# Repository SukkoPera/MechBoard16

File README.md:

# MechBoard16

MechBoard16 is a mechanical keyboard for the Commodore 16.

## Summary
This project was born out of my dream of being able to build a complete Commodore 16 computer from scratch. While you can already build [the full circuit board](https://github.com/SukkoPera/LittleSixteen) from off-the-shelf-components only and put that in a case you can buy new on the market (either [Breadbin](https://www.retrofuzion.com/products/breadbin-case-set) or [C64c-style](https://icomp.de/shop-icomp/en/shop/product/c64c-case.html)), you would then have to complete that by stealing a keyboard from an original machine (and no, VIC-20/C64 keyboards won't work and there isn't much we can do in that regard, unless we patch the KERNAL and a ton of software). So I just set to rectify that.

Now, while I'm not too fussy when it comes to keyboards, give me anything that works and I'll be happy (although you probably wouldn't want to be one of the witnesses of the third time I typed *rep* on a keyboard with a misworking <kbd>G</kbd>...), making the new C16 keyboard a mechanical one looked to be the best choice for a number of reasons:
- Some good soul has already done that for the C64: he did the basic design, took all the relevant measurements, thought about all the parts needed and - best of all - he openly shared all of his notes and materials about the process. Since his original project fits the Breadbin C64 and the C16 case is basically the same, this means that, in principle, I could recycle 90% of his work and just design a new PCB featuring the C16 keyboard matrix. So all hail to MtnBuffalo and his <a href="https://www.breadbox64.com/MechBoard64-2/">MechBoard64 project</a>, this wouldn't be a reality without his job, isn't openness great?
- Well, designing a membrane keyboard would actually be harder for an amateur (all membranes are custom, how do I design and get one produced?) and lead inferior results.
- There is an incredible variety of mechanical keyswitches and keycaps around, yielding endless customization possibilities.
- I didn't know anything about mechanical keyboards, so it would just be fun to learn about them and finally own one at last.

## Assembly
The documentation from MtnBuffalo is pretty detailed, so please refer to that but first have a look at the following notes from myself.

### Circuit Board
The **circuit board** is the electrical heart of the keyboard and is the only component that needs to be different from the one used in MechBoard64 since the C16 and C64 use different keyboard matrices, despite the nearly identical key layout.

The MechBoard64 PCB was designed in a non-open format, so I redid it all in KiCad and while I was at it, I decided to add some improvements:
- I added a diode for every key. In theory, this allows for every key to be read properly, without *ghosting* issues. Still, the KERNAL applies a *blocking* algorithm so, in practice, nothing will change in this regard.
- BUT I also added a microcontroller with USB capabilities (ATmega32U4) and connected it to all the keyboard rows and columns. This mean the whole thing can be a *N-Key Rollover* USB keyboard, which will probably be useful for those people who want to use it with emulators. And keep in mind that since you have full control on the software, it can also appear as a VIC-20/C64 keyboard over USB!
- MechBoard64 has a version with LEDs, but all LEDs are driven in parallel, resulting in a huge current draw. I don't particularly care about LEDs but I decided to throw them in while I was at it, and since I would have a microcontroller onboard anyway, I decided to drive them through a MAX7219/7221 chip: this allows for individual LED control, much reduced power draw (the LEDs are multiplexed), brightness control and maximum brightness setting through a single resistor.
- I have slightly revised the Shift Lock circuit: this is necessary because latching key switches are uncommon, so one cannot be found, the behavior of the original key must be achieved through electronics. Make sure to set the JP2 and JP3 jumpers according to whether you managed to find a real latching key switch or you are using an ordinary (= momentary) one.

I realize not everyone might be interested in the above and in fact **it is all optional**! If you are not interested in USB and/or LEDs, just mount the key switches and bridge every diode (yes, this is annoying, sorry), ignoring all the extra components: basic keyboard functionality will still be there.

The PCB is what this GitHub project is all about and let me reinstate that it's only component that you need to change to make a MechBoard64 work on a C16. If you are already familiar with it, just grab the new PCB and go ahead with the build!

### Firmware
If you have installed the ATmega32U4 microcontroller, you will need to flash some firmware on it: this is available [in a separate repository](https://github.com/SukkoPera/Mechware16) and is based on the Arduino platform, so you will need the [Arduino software](https://www.arduino.cc/en/software/) to flash it. I used legacy version 1.8.19 so I can only guarantee that that one works, if you use a newer one or the web-based IDE you are on your own.

You will need to install the bootloader first. For this you will need an ICSP programmer, which you can buy cheaply on AliExpress or similar sites. The ICSP connector is marked as J202 on the board. Select the _Arduino Micro_ board in the IDE and proceed as normal. Once that is done, the firmware can be flashed through USB connector J201 as if the whole thing were a normal Arduino Micro board. Make sure to install the dependencies first.

### Metal Bracket
The board will need to be fastened to the top part of the case somehow, and this is done through a **metal bracket** which doubles as a keyboard plate.

I have designed [my own bracket](https://github.com/SukkoPera/MechPlate16) based on MtnBuffalo's instructions, but since I strived to maintain the same position for all of the key and screw holes, you should be able to use this board with the plate that was designed for the MechBoard64: you can get it through a Chinese company as MtnBuffalo recommends or ask other manufacturers.

### Screws
To fasten the two things together, you will need **screws**: MtnBuffalo recommends *six plastic M3 x 10 mm screws, six plastic M3 bolts and six plastic M3 x 3mm spacers (ø=6 mm)*. I used *metal* screws of the same dimensions and plastic spacers with an outside diameter of 5 mm, putting some insulation tape on the washers in order to avoid them shorting tracks on the PCB.

### Key Switches
At this point you will have a nice keyboard prototype without keys, so you will need to solder exactly 66 **key switches** into it. This is the point where your customization options start: MtnBuffalo used *Gateron Yellow* switches as he thought they yield a very similar experience to the original keys. Personally, I don't think we should necessarily aim at replicating the original experience, so I'd recommend feeling free to use different switches.

While the keyboard was designed for Cherry MX keyswitches, these days maaaany manufacturers make compatible ones: I think the most respected alternative manufacturers are <a href="https://www.gateron.com">Gateron</a> and <a href="https://www.kailh.net">Kailh</a>. *Durock* is another well-known brand and, even though I don't think it's a particularly smart idea to save 10€ on a project that will cost you around 100€ anyway, there are also cheaper options: *Outemu* is a Chinese brand that seems to have its fans, while *Redragon* is the cheapest I could find (less than 10€ for 150 keyswitches - more than enough for 2 keyboard - shipped to Europe!) and their Red switches look definitely better to me, than what the price would suggest.

Here are a few links to online shops where you can find an ample offering of key switches:
- [Keychron](https://www.keychron.com)
- [CannonKeys](https://cannonkeys.com/collections/switches)

Even by just skimming through these shops, it is easy to get lost for those like me who might not be too much into keyboards, so here's some help: first of all, you need *standard/normal profile* switches, don't get *low profile* ones.

Second: there are 3 main types of switches, giving different "press feelings": the most common type is *linear* and the original keys are of this type (get this if you are undecided). It means that the key can be pressed with a constant pressure until it comes to a halt. Some people prefer to feel a "bump" when the key triggers, so they'd better look for switches of the *tactile* type (personally, I find this to be really annoying unless you are used to it). Finally, I have a thing for *clicky* switches, which make a rather loud click when they trigger (this is what most people find annoying, but when your ordinary keyboard is a 122-key "battlecruiser" Model M...).

Then it basically gets down to how hard you want to push your keys, which is measured in grams: generally 35g is the softest option, while 80g is the stiffest you can get.

These two parameters we just mentioned are usually reflected in the color of the switch *stem*. There is some informal standard across manufacturers for this (derived from the original Cherry MX catalogue, I think), but always double check: blue is for clicky switches, red is for soft linears, black is for stiff linears, etc.

Speaking of the stem, you'll notice that the MX stem is a simple cross. Sometimes the cross might include walls on its sides or all around: these are just for dust protection, which seems totally redundant to me but there you go. Just make sure it's still MX-compatible.

MX-compatible key switches can have two different mounting styles, *PCB* or *plate*: the former are for keyboards that do not use a plate and come with two extra side prongs that help positioning the key switch correctly and securing it in place. Plate-mount switches lack these prongs, since their job will be done by the hole in the plate. MechBoard64 requires plate-mount switches or that you cut the extra prongs (it's just plastic), while **MechBoard16 has extra holes** and will thus accept both types.

One final tip is that there is a tendency to use stiffer switches for the spacebar, since it is generally pressed with more force. So if you choose *Red* switches, you might want to use a *Black* one for the spacebar. Due to my clicky thing, I used *Gateron Blue*'s but I went with a *Green* for my spacebar.

### Keycaps
The key switches look all boringly the same, so you'll probably want to stick some **keycaps** on their stem*. I was quite surprised when I found out that almost all keycaps ever made are the same size, so **in principle** you could use any keycaps having MX connection style. In reality, you are bound to the original Commodore keycaps: this is because most of the wider keycaps (<kbd>CTRL</kbd>, <kbd>CLEAR/HOME</kbd>, <kbd>SHIFT</kbd> and the Function keys) on the original keyboard have their stem receptacles off-center while contemporary keycaps, on the contrary, have the receptacles centered.

There are more problems in using modern keycaps by the way: for instance, the original Commodore spacebar is 9U, while contemporary spacebars are shorter (I think they don't go over 7U). Most modern keycaps also have different profiles for different rows (the originals are all the same) and not all sizes are available for all rows: as an example, for the Function keys you'll need 1.5U keycaps, one per row, but modern keycaps only come in 1.5U for rows 1 and 3.

Since working around all these issues requires more thought and since the MechBoard64 simply used the original Commodore placement, for the first MechBoard16 release I decided to follow suit but things might change in the future, once I'm sure all the rest is correct.

The bottom line is that **at the moment you still need to recover the keys from an original C16 keyboard**. Keys from a VIC-20 or C64 keyboard should work just as well, despite having some labeling differences (<kbd>RESTORE</kbd> is <kbd>CLEAR/HOME</kbd>, the arrow keys are missing, etc.). Some people have actually produced new C64 keys but they didn't plan alternative labeling for us C16 users and apparently those keys were even only sold through Kickstarter-style initiatives and are not on regular sale (yet?).

### Keycap Adapters
It looked easy after all, didn't it? Unfortunately, the original Commodore keycaps do not have MX-style stems, so you'll need some **adapters**. These must be 3D-printed, use the STL file provided by MechBoard64.

### Stabilizers
The wider keys (<kbd>RETURN</kbd> and <kbd>SPACE</kbd>) are too large for a single keyswitch and would *bind* (get stuck) unless hit close to the center. In order to avoid that, thin metal bars are used to attach them to the keyboard plate for the whole length. These are called **stabilizers** and again, come in different styles. MechBoard64 went for the so-called *Costar stabilizers* and we did the same: these can be bought on the market and come as a kit of plastic clips that must be inserted in the slots available on the plate, a set of key inserts and some bent metal wire that goes inbetween.

Unfortunately, the original Commodore spacebar is too wide for the stabilizer kits that are currently available commercially so, while you can use the clips and inserts, you will need to bend some metal wire with the correct proportions. MtnBuffalo used 1 mm steel wire bent with a tool named EZ Bender and I was able to buy both things at a model shop (I was told they are commonly used by model airplane enthusiasts, if that helps). The EZ Bender was about 30€ and the wire is inexpensive (buy it straight, not in a spool!).

### Cables
This is the easy part: just get a bunch of those *Dupont wires* people use for Arduino projects: you'll need 20 female-to-female, they're cheap and you can find them everywhere. You'll probably find them with individual connectors only but oh well... As for the length, 20 cm should be fine.

The above assumes that a 90-degree male pin header is soldered at CN1, but you can also solder a female header and use male-to-female wires if so you prefer.

Oh, and while we're at it, CN2 on the board allows for connection of the keyboard to a Plus/4 computer: while this makes little sense, as the Plus/4 has a totally different form factor in which the keyboard cannot fit, it could still be useful for temporary use or whatever. Maybe someone will re-layout the board in the proper format? ;)

### LEDs
If you want LEDs, you can solder one per each key. The required diameter is 3 mm. I'd recommend using high-brightness ones.

Remember to tune R207 according to the LEDs you choose and brightness you like.

To tune the brightness to your liking, you first need to change R207 according to table 11 of the [MAX7219/7221 datasheet](https://www.analog.com/media/en/technical-documentation/data-sheets/max7219-max7221.pdf). This will set the maximum brightness of the LEDs of all keys except <kbd>SHIFT</kbd>, <kbd>SHIFT LOCK</kbd> and <kbd>SPACE</kbd>. The actual brightness can be fine-tuned through some hotkeys (see below).

Due to its length, the spacebar has 3 LEDs which are linked together: they are all either ON or OFF at any given moment. The same goes for the LEDs for the two <kbd>SHIFT</kbd> keys. The brightness for these is controlled by resistors R208, 209, 210, 211 and 212. These can all be set to the same value, which you should calculate depending on the Vf of the LEDs you are using and the current you set with R207, so that these LEDs have the same brightness as the other ones.

The LED for the <kbd>SHIFT LOCK</kbd> key only lights up when the lock is enabled. Its brightness is controlled by R3, set it to same value as R208/etc., unless you are using a different led for this key.

Since I was tired of having to disconnect both the keyboard and the case LED every time I had to open the machine, I added a connector so that the case LED can be connected to the keyboard board, namely R204, black wire goes to GND. You can even replace the built-in LED with an RGB one and set it to your favourite color by picking appropriate values for R204/205/206 (for R/G/B respectively). This LED can also be controlled by the software running on the microcontroller, so maybe it could be used for signalling some events. Note that the R204 will not do anything if the ATmega32U4 microcontroller is not mounted.

### HotKeys
The firmware supports some hotkeys, all triggered by pressing <kbd>CTRL</kbd> + <kbd>C=</kbd> + a third key, as follows:
- <kbd>F1</kbd>: Turn all LEDs permanently OFF.
- <kbd>F2</kbd>: Turn all LEDs permanently ON.
- <kbd>F3</kbd>: Turn all LEDS OFF, but turn ON those corresponding to the keys that are being pressed.
- <kbd>F4</kbd>: Turn all LEDS ON, but turn OFF those corresponding to the keys that are being pressed.
- <kbd>1</kbd>: Set startup animation to *Chasing*.
- <kbd>2</kbd>: Set startup animation to *Scrolling Column*.
- <kbd>+</kbd>: Increase LED brightness.
- <kbd>-</kbd>: Decrease LED brightness.

## Mainboard Modification
Unfortunately a stock C16 does not feature any power pins on the keyboard connector, therefore a small modification must be made on the mainboard: just solder a wire on the back of the board as in [this picture](img/mech_power_photo.jpg). Make sure it doesn't touch the nearby pins.

Note that this could be made even easier as the large track below the keyboard connector on the board is +5V, but you would need to scrape away some insulation and I like fully reversible mods anyway.

If you are using a LittleSixteen board, this modification is not necessary since V4, just short the JP1 solder jumper.

## Disclaimer
**NOTE: I am in no way affiliated with or endorsed by any of the above-mentioned companies, shops or websites. I am only suggesting them for practical needs and to save you time.**

## Releases
If you want to get this board produced, you are recommended to get [the latest release](https://github.com/SukkoPera/MechBoard16/releases) rather than the current git version, as the latter might be under development and is not guaranteed to be working.

Every release is accompanied by its Bill Of Materials (BOM) file and any relevant notes about it, which you are recommended to read carefully.

## License
The MechBoard16 documentation, including the design itself, is copyright &copy; SukkoPera 2023-2025 and is licensed under the [Creative Commons Attribution-NonCommercial-ShareAlike 4.0 International License](https://creativecommons.org/licenses/by-nc-sa/4.0/).

This documentation is distributed *as is* and WITHOUT ANY EXPRESS OR IMPLIED WARRANTIES whatsoever with respect to its functionality, operability or use, including, without limitation, any implied warranties OF MERCHANTABILITY, SATISFACTORY QUALITY, FITNESS FOR A PARTICULAR PURPOSE or infringement. We expressly disclaim any liability whatsoever for any direct, indirect, consequential, incidental or special damages, including, without limitation, lost revenues, lost profits, losses resulting from business interruption or loss of data, regardless of the form of action or legal theory under which the liability may be asserted, even if advised of the possibility or likelihood of such damages.

## Support the Project
If you want to get some boards manufactured, you can get them from PCBWay through this link:

You get my gratitude and cheap, professionally-made and good quality PCBs, I get some credit that will help with this and [other projects](https://www.pcbway.com/project/member/shareproject/?bmbid=41100). You won't even have to worry about the various PCB options, it's all pre-configured for you!

Also, if you still have to register, [you can use this link](https://www.pcbway.com/setinvite.aspx?inviteid=41100) to get some bonus initial credit (and yield me some more).

You can also buy me a coffee if you want:

## Thanks
- MtnBuffalo for designing the original MechBoard64, making it open and being always happy to help.

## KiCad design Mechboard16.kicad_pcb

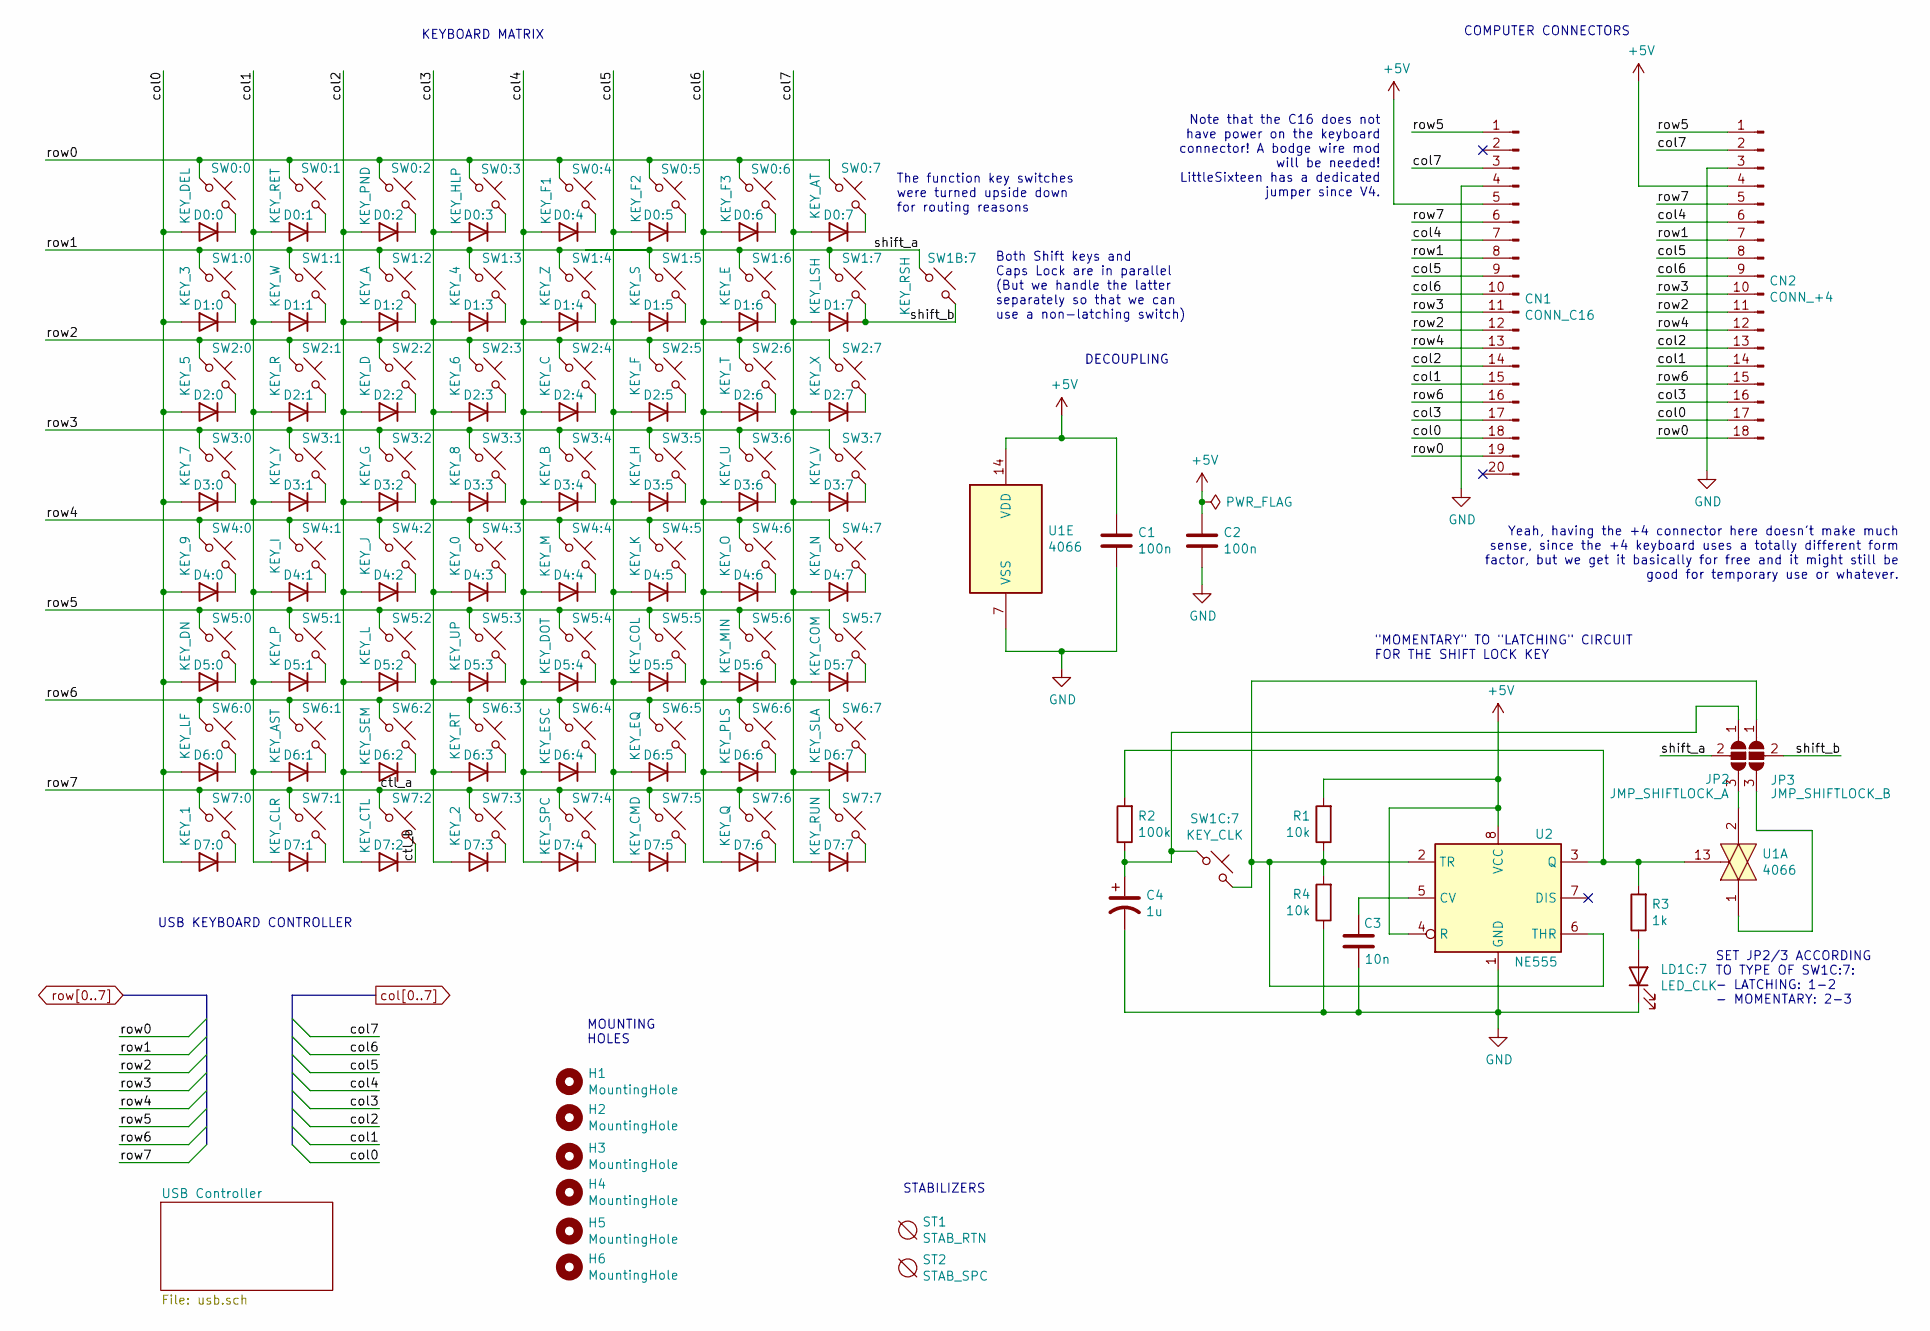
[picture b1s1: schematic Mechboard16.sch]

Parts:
C1, C2: 100n; C_0805_2012Metric_Pad1.18x1.45mm_HandSolder; LCSC C49678
C3: 10n; C_0805_2012Metric_Pad1.18x1.45mm_HandSolder; LCSC C1710
C4: 1u; C_1206_3216Metric_Pad1.33x1.80mm_HandSolder; LCSC C1848
CN1: CONN_C16; PinHeader_1x20_P2.54mm_Vertical
CN2: CONN_+4; PinHeader_1x18_P2.54mm_Vertical
D0:0, D0:1, D0:2, D0:3, D0:4, D0:5, D0:6, D0:7, D1:0, D1:1, D1:2, D1:3, D1:4, D1:5, D1:6, D1:7, D2:0, D2:1, D2:2, D2:3, D2:4, D2:5, D2:6, D2:7, D3:0, D3:1, D3:2, D3:3, D3:4, D3:5, D3:6, D3:7, D4:0, D4:1, D4:2, D4:3, D4:4, D4:5, D4:6, D4:7, D5:0, D5:1, D5:2, D5:3, D5:4, D5:5, D5:6, D5:7, D6:0, D6:1, D6:2, D6:3, D6:4, D6:5, D6:6, D6:7, D7:0, D7:1, D7:2, D7:3, D7:4, D7:5, D7:6, D7:7: 1n4148; D_SOD-323_HandSoldering; LCSC C2128
H1, H2, H3, H4, H5, H6: MountingHole; MountingHole_3.5mm
JP2: JMP_SHIFTLOCK_A; SolderJumper-3_P1.3mm_Open_RoundedPad1.0x1.5mm
JP3: JMP_SHIFTLOCK_B; SolderJumper-3_P1.3mm_Open_RoundedPad1.0x1.5mm
LD1C:7: LED_CLK; LED_MX_6028R; LCSC C3646964
R1, R4: 10k; R_0805_2012Metric_Pad1.20x1.40mm_HandSolder; LCSC C17414
R2: 100k; R_0805_2012Metric_Pad1.20x1.40mm_HandSolder; LCSC C149504
R3: 1k; R_0805_2012Metric_Pad1.20x1.40mm_HandSolder; LCSC C17513
ST1: STAB_RTN; Stabilizer_Costar_2.00u
ST2: STAB_SPC; Stabilizer_Costar_9.00u_Commodore
SW0:0: KEY_DEL; SW_Hotswap_Kailh_MX_1.00u; LCSC C41430893
SW0:1: KEY_RET; SW_Hotswap_Kailh_MX_2.00u; LCSC C41430893
SW0:2: KEY_PND; SW_Hotswap_Kailh_MX_1.00u; LCSC C41430893
SW0:3: KEY_HLP; SW_Hotswap_Kailh_MX_1.50u_OffsetL; LCSC C41430893
SW0:4: KEY_F1; SW_Hotswap_Kailh_MX_1.50u_OffsetL; LCSC C41430893
SW0:5: KEY_F2; SW_Hotswap_Kailh_MX_1.50u_OffsetL; LCSC C41430893
SW0:6: KEY_F3; SW_Hotswap_Kailh_MX_1.50u_OffsetL; LCSC C41430893
SW0:7: KEY_AT; SW_Hotswap_Kailh_MX_1.00u; LCSC C41430893
SW1:0: KEY_3; SW_Hotswap_Kailh_MX_1.00u; LCSC C41430893
SW1:1: KEY_W; SW_Hotswap_Kailh_MX_1.00u; LCSC C41430893
SW1:2: KEY_A; SW_Hotswap_Kailh_MX_1.00u; LCSC C41430893
SW1:3: KEY_4; SW_Hotswap_Kailh_MX_1.00u; LCSC C41430893
SW1:4: KEY_Z; SW_Hotswap_Kailh_MX_1.00u; LCSC C41430893
SW1:5: KEY_S; SW_Hotswap_Kailh_MX_1.00u; LCSC C41430893
SW1:6: KEY_E; SW_Hotswap_Kailh_MX_1.00u; LCSC C41430893
SW1:7: KEY_LSH; SW_Hotswap_Kailh_MX_1.50u_OffsetL; LCSC C41430893
SW1B:7: KEY_RSH; SW_Hotswap_Kailh_MX_1.50u_OffsetL; LCSC C41430893
SW1C:7: KEY_CLK; SW_Hotswap_Kailh_MX_1.00u; LCSC C41430893
SW2:0: KEY_5; SW_Hotswap_Kailh_MX_1.00u; LCSC C41430893
SW2:1: KEY_R; SW_Hotswap_Kailh_MX_1.00u; LCSC C41430893
SW2:2: KEY_D; SW_Hotswap_Kailh_MX_1.00u; LCSC C41430893
SW2:3: KEY_6; SW_Hotswap_Kailh_MX_1.00u; LCSC C41430893
SW2:4: KEY_C; SW_Hotswap_Kailh_MX_1.00u; LCSC C41430893
SW2:5: KEY_F; SW_Hotswap_Kailh_MX_1.00u; LCSC C41430893
SW2:6: KEY_T; SW_Hotswap_Kailh_MX_1.00u; LCSC C41430893
SW2:7: KEY_X; SW_Hotswap_Kailh_MX_1.00u; LCSC C41430893
SW3:0: KEY_7; SW_Hotswap_Kailh_MX_1.00u; LCSC C41430893
SW3:1: KEY_Y; SW_Hotswap_Kailh_MX_1.00u; LCSC C41430893
SW3:2: KEY_G; SW_Hotswap_Kailh_MX_1.00u; LCSC C41430893
SW3:3: KEY_8; SW_Hotswap_Kailh_MX_1.00u; LCSC C41430893
SW3:4: KEY_B; SW_Hotswap_Kailh_MX_1.00u; LCSC C41430893
SW3:5: KEY_H; SW_Hotswap_Kailh_MX_1.00u; LCSC C41430893
SW3:6: KEY_U; SW_Hotswap_Kailh_MX_1.00u; LCSC C41430893
SW3:7: KEY_V; SW_Hotswap_Kailh_MX_1.00u; LCSC C41430893
SW4:0: KEY_9; SW_Hotswap_Kailh_MX_1.00u; LCSC C41430893
SW4:1: KEY_I; SW_Hotswap_Kailh_MX_1.00u; LCSC C41430893
SW4:2: KEY_J; SW_Hotswap_Kailh_MX_1.00u; LCSC C41430893
SW4:3: KEY_0; SW_Hotswap_Kailh_MX_1.00u; LCSC C41430893
SW4:4: KEY_M; SW_Hotswap_Kailh_MX_1.00u; LCSC C41430893
SW4:5: KEY_K; SW_Hotswap_Kailh_MX_1.00u; LCSC C41430893
SW4:6: KEY_O; SW_Hotswap_Kailh_MX_1.00u; LCSC C41430893
SW4:7: KEY_N; SW_Hotswap_Kailh_MX_1.00u; LCSC C41430893
SW5:0: KEY_DN; SW_Hotswap_Kailh_MX_1.00u; LCSC C41430893
SW5:1: KEY_P; SW_Hotswap_Kailh_MX_1.00u; LCSC C41430893
SW5:2: KEY_L; SW_Hotswap_Kailh_MX_1.00u; LCSC C41430893
SW5:3: KEY_UP; SW_Hotswap_Kailh_MX_1.00u; LCSC C41430893
SW5:4: KEY_DOT; SW_Hotswap_Kailh_MX_1.00u; LCSC C41430893
SW5:5: KEY_COL; SW_Hotswap_Kailh_MX_1.00u; LCSC C41430893
SW5:6: KEY_MIN; SW_Hotswap_Kailh_MX_1.00u; LCSC C41430893
SW5:7: KEY_COM; SW_Hotswap_Kailh_MX_1.00u; LCSC C41430893
SW6:0: KEY_LF; SW_Hotswap_Kailh_MX_1.00u; LCSC C41430893
SW6:1: KEY_AST; SW_Hotswap_Kailh_MX_1.00u; LCSC C41430893
SW6:2: KEY_SEM; SW_Hotswap_Kailh_MX_1.00u; LCSC C41430893
SW6:3: KEY_RT; SW_Hotswap_Kailh_MX_1.00u; LCSC C41430893
SW6:4: KEY_ESC; SW_Hotswap_Kailh_MX_1.00u; LCSC C41430893
SW6:5: KEY_EQ; SW_Hotswap_Kailh_MX_1.00u; LCSC C41430893
SW6:6: KEY_PLS; SW_Hotswap_Kailh_MX_1.00u; LCSC C41430893
SW6:7: KEY_SLA; SW_Hotswap_Kailh_MX_1.00u; LCSC C41430893
SW7:0: KEY_1; SW_Hotswap_Kailh_MX_1.00u; LCSC C41430893
SW7:1: KEY_CLR; SW_Hotswap_Kailh_MX_1.50u_OffsetR; LCSC C41430893
SW7:2: KEY_CTL; SW_Hotswap_Kailh_MX_1.50u_OffsetL; LCSC C41430893
SW7:3: KEY_2; SW_Hotswap_Kailh_MX_1.00u; LCSC C41430893
SW7:4: KEY_SPC; SW_Hotswap_Kailh_MX_9.00u; LCSC C41430893
SW7:5: KEY_CMD; SW_Hotswap_Kailh_MX_1.00u; LCSC C41430893
SW7:6: KEY_Q; SW_Hotswap_Kailh_MX_1.00u; LCSC C41430893
SW7:7: KEY_RUN; SW_Hotswap_Kailh_MX_1.00u; LCSC C41430893
U1: 4066; SOIC-14_3.9x8.7mm_P1.27mm; LCSC C233577
U2: NE555; SOIC-8_3.9x4.9mm_P1.27mm; LCSC C5125085

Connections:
+5V: C1.1, C2.1, CN1.5, CN2.4, R1.2, U1.14 (VDD), U2.4 (R), U2.8 (VCC); also elsewhere on the board
/ctl_b: D7:2.1 (K), SW7:2.2
/shift_b: D1:7.1 (K), JP2.2 (C), SW1:7.2, SW1B:7.2
GND: C1.2, C2.2, C3.2, C4.2, CN1.4, CN2.3, LD1C:7.1 (K), R4.1, U1.7 (VSS), U2.1 (GND); also elsewhere on the board
unnamed: C3.1, U2.5 (CV)
unnamed: C4.1, JP3.1 (A), R2.1, SW1C:7.1
unnamed: D0:0.1 (K), SW0:0.2
unnamed: D0:1.1 (K), SW0:1.2
unnamed: D0:2.1 (K), SW0:2.2
unnamed: D0:3.1 (K), SW0:3.2
unnamed: D0:4.1 (K), SW0:4.2
unnamed: D0:5.1 (K), SW0:5.2
unnamed: D0:6.1 (K), SW0:6.2
unnamed: D0:7.1 (K), SW0:7.2
unnamed: D1:0.1 (K), SW1:0.2
unnamed: D1:1.1 (K), SW1:1.2
unnamed: D1:2.1 (K), SW1:2.2
unnamed: D1:3.1 (K), SW1:3.2
unnamed: D1:4.1 (K), SW1:4.2
unnamed: D1:5.1 (K), SW1:5.2
unnamed: D1:6.1 (K), SW1:6.2
unnamed: D2:0.1 (K), SW2:0.2
unnamed: D2:1.1 (K), SW2:1.2
unnamed: D2:2.1 (K), SW2:2.2
unnamed: D2:3.1 (K), SW2:3.2
unnamed: D2:4.1 (K), SW2:4.2
unnamed: D2:5.1 (K), SW2:5.2
unnamed: D2:6.1 (K), SW2:6.2
unnamed: D2:7.1 (K), SW2:7.2
unnamed: D3:0.1 (K), SW3:0.2
unnamed: D3:1.1 (K), SW3:1.2
unnamed: D3:2.1 (K), SW3:2.2
unnamed: D3:3.1 (K), SW3:3.2
unnamed: D3:4.1 (K), SW3:4.2
unnamed: D3:5.1 (K), SW3:5.2
unnamed: D3:6.1 (K), SW3:6.2
unnamed: D3:7.1 (K), SW3:7.2
unnamed: D4:0.1 (K), SW4:0.2
unnamed: D4:1.1 (K), SW4:1.2
unnamed: D4:2.1 (K), SW4:2.2
unnamed: D4:3.1 (K), SW4:3.2
unnamed: D4:4.1 (K), SW4:4.2
unnamed: D4:5.1 (K), SW4:5.2
unnamed: D4:6.1 (K), SW4:6.2
unnamed: D4:7.1 (K), SW4:7.2
unnamed: D5:0.1 (K), SW5:0.2
unnamed: D5:1.1 (K), SW5:1.2
unnamed: D5:2.1 (K), SW5:2.2
unnamed: D5:3.1 (K), SW5:3.2
unnamed: D5:4.1 (K), SW5:4.2
unnamed: D5:5.1 (K), SW5:5.2
unnamed: D5:6.1 (K), SW5:6.2
unnamed: D5:7.1 (K), SW5:7.2
unnamed: D6:0.1 (K), SW6:0.2
unnamed: D6:1.1 (K), SW6:1.2
unnamed: D6:2.1 (K), SW6:2.2
unnamed: D6:3.1 (K), SW6:3.2
unnamed: D6:4.1 (K), SW6:4.2
unnamed: D6:5.1 (K), SW6:5.2
unnamed: D6:6.1 (K), SW6:6.2
unnamed: D6:7.1 (K), SW6:7.2
unnamed: D7:0.1 (K), SW7:0.2
unnamed: D7:1.1 (K), SW7:1.2
unnamed: D7:3.1 (K), SW7:3.2
unnamed: D7:4.1 (K), SW7:4.2
unnamed: D7:5.1 (K), SW7:5.2
unnamed: D7:6.1 (K), SW7:6.2
unnamed: D7:7.1 (K), SW7:7.2
unnamed: JP2.1 (A), R1.1, R4.2, SW1C:7.2, U2.2 (TR), U2.6 (THR)
unnamed: JP2.3 (B), U1.1
unnamed: JP3.3 (B), U1.2
unnamed: LD1C:7.2 (A), R3.1
unnamed: R2.2, R3.2, U1.13, U2.3 (Q)
col0: CN1.18, CN2.17, D0:0.2 (A), D1:0.2 (A), D2:0.2 (A), D3:0.2 (A), D4:0.2 (A), D5:0.2 (A), D6:0.2 (A), D7:0.2 (A); also elsewhere on the board
col1: CN1.15, CN2.14, D0:1.2 (A), D1:1.2 (A), D2:1.2 (A), D3:1.2 (A), D4:1.2 (A), D5:1.2 (A), D6:1.2 (A), D7:1.2 (A); also elsewhere on the board
col2: CN1.14, CN2.13, D0:2.2 (A), D1:2.2 (A), D2:2.2 (A), D3:2.2 (A), D4:2.2 (A), D5:2.2 (A), D6:2.2 (A), D7:2.2 (A); also elsewhere on the board
col3: CN1.17, CN2.16, D0:3.2 (A), D1:3.2 (A), D2:3.2 (A), D3:3.2 (A), D4:3.2 (A), D5:3.2 (A), D6:3.2 (A), D7:3.2 (A); also elsewhere on the board
col4: CN1.7, CN2.6, D0:4.2 (A), D1:4.2 (A), D2:4.2 (A), D3:4.2 (A), D4:4.2 (A), D5:4.2 (A), D6:4.2 (A), D7:4.2 (A); also elsewhere on the board
col5: CN1.9, CN2.8, D0:5.2 (A), D1:5.2 (A), D2:5.2 (A), D3:5.2 (A), D4:5.2 (A), D5:5.2 (A), D6:5.2 (A), D7:5.2 (A); also elsewhere on the board
col6: CN1.10, CN2.9, D0:6.2 (A), D1:6.2 (A), D2:6.2 (A), D3:6.2 (A), D4:6.2 (A), D5:6.2 (A), D6:6.2 (A), D7:6.2 (A); also elsewhere on the board
col7: CN1.3, CN2.2, D0:7.2 (A), D1:7.2 (A), D2:7.2 (A), D3:7.2 (A), D4:7.2 (A), D5:7.2 (A), D6:7.2 (A), D7:7.2 (A); also elsewhere on the board
row0: CN1.19, CN2.18, SW0:0.1, SW0:1.1, SW0:2.1, SW0:3.1, SW0:4.1, SW0:5.1, SW0:6.1, SW0:7.1; also elsewhere on the board
row1: CN1.8, CN2.7, JP3.2 (C), SW1:0.1, SW1:1.1, SW1:2.1, SW1:3.1, SW1:4.1, SW1:5.1, SW1:6.1, SW1:7.1, SW1B:7.1; also elsewhere on the board
row2: CN1.12, CN2.11, SW2:0.1, SW2:1.1, SW2:2.1, SW2:3.1, SW2:4.1, SW2:5.1, SW2:6.1, SW2:7.1; also elsewhere on the board
row3: CN1.11, CN2.10, SW3:0.1, SW3:1.1, SW3:2.1, SW3:3.1, SW3:4.1, SW3:5.1, SW3:6.1, SW3:7.1; also elsewhere on the board
row4: CN1.13, CN2.12, SW4:0.1, SW4:1.1, SW4:2.1, SW4:3.1, SW4:4.1, SW4:5.1, SW4:6.1, SW4:7.1; also elsewhere on the board
row5: CN1.1, CN2.1, SW5:0.1, SW5:1.1, SW5:2.1, SW5:3.1, SW5:4.1, SW5:5.1, SW5:6.1, SW5:7.1; also elsewhere on the board
row6: CN1.16, CN2.15, SW6:0.1, SW6:1.1, SW6:2.1, SW6:3.1, SW6:4.1, SW6:5.1, SW6:6.1, SW6:7.1; also elsewhere on the board
row7: CN1.6, CN2.5, SW7:0.1, SW7:1.1, SW7:2.1, SW7:3.1, SW7:4.1, SW7:5.1, SW7:6.1, SW7:7.1; also elsewhere on the board

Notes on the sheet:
KEYBOARD MATRIX
Both Shift keys and Caps Lock are in parallel (But we handle the latter separately so that we can use a non-latching switch)
DECOUPLING
"MOMENTARY" TO "LATCHING" CIRCUIT FOR THE SHIFT LOCK KEY
COMPUTER CONNECTORS
Yeah, having the +4 connector here doesn't make much sense, since the +4 keyboard uses a totally different form factor, but we get it basically for free and it might still be good for temporary use or whatever.
SET JP2/3 ACCORDING TO TYPE OF SW1C:7: - LATCHING: 1-2 - MOMENTARY: 2-3
Note that the C16 does not have power on the keyboard connector! A bodge wire mod will be needed! LittleSixteen has a dedicated jumper since V4.
MOUNTING HOLES
USB KEYBOARD CONTROLLER
STABILIZERS
The function key switches were turned upside down for routing reasons

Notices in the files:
README.md:
License:
The MechBoard16 documentation, including the design itself, is copyright © SukkoPera 2023-2025 and is licensed under the [Creative Commons Attribution-NonCommercial-ShareAlike 4.0 International License](https://creativecommons.org/licenses/by-nc-sa/4.0/).
This documentation is distributed *as is* and WITHOUT ANY EXPRESS OR IMPLIED WARRANTIES whatsoever with respect to its functionality, operability or use, including, without limitation, any implied warranties OF MERCHANTABILITY, SATISFACTORY QUALITY, FITNESS FOR A PARTICULAR PURPOSE or infringement. We expressly disclaim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
